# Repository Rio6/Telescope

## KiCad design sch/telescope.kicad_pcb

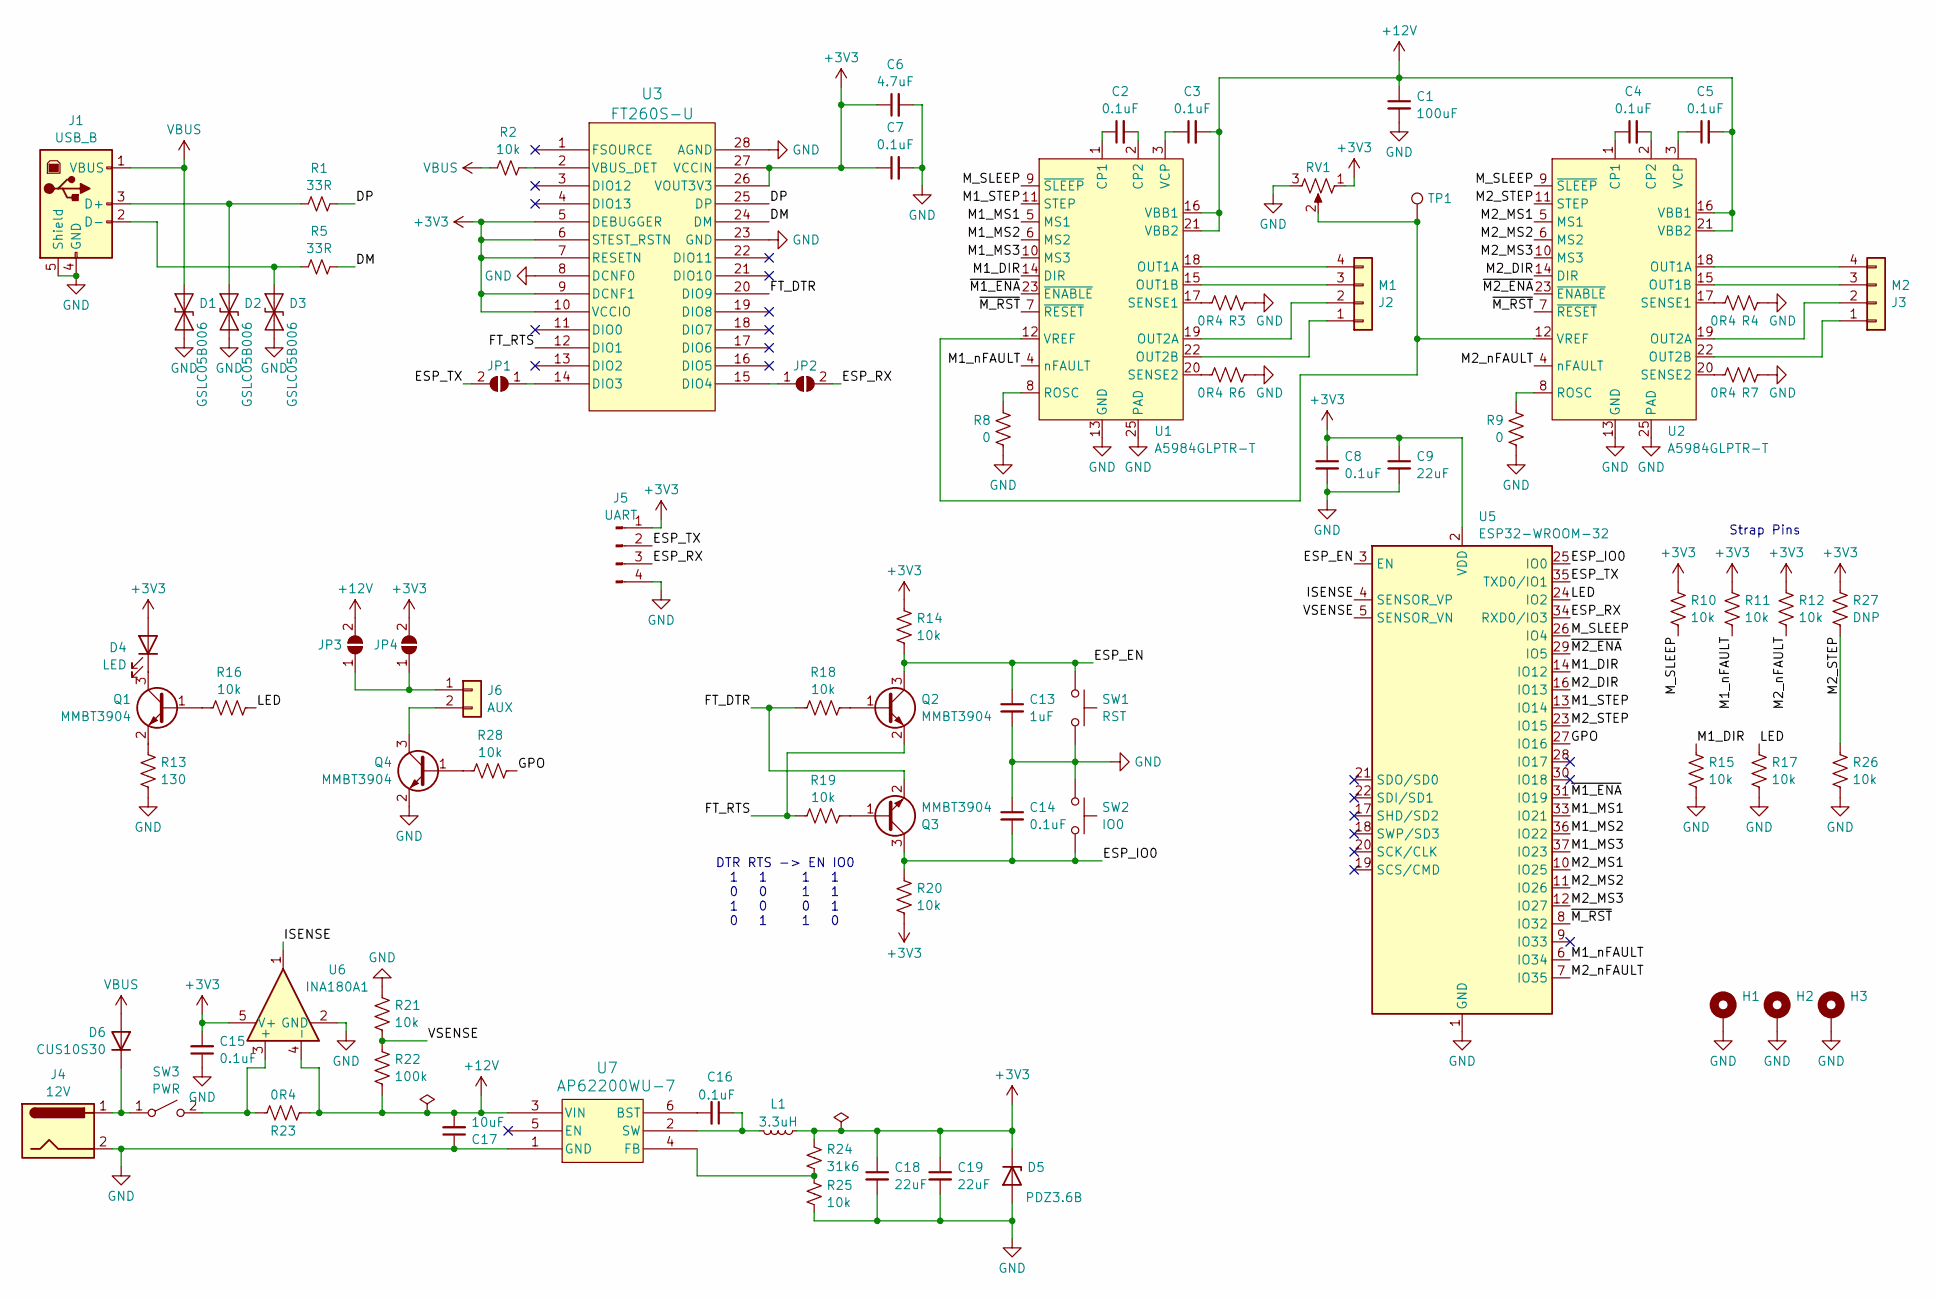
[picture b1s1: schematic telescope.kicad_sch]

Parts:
C1: 100uF; C_Radial_D5.0mm_H7.0mm_P2.00mm
C2, C3, C4, C5, C7, C8, C14, C15, C16: 0.1uF; C_0805_2012Metric_Pad1.18x1.45mm_HandSolder; Digikey PN 311-1140-1-ND
C6: 4.7uF; C_0805_2012Metric_Pad1.18x1.45mm_HandSolder; Digikey PN 1276-1244-1-ND
C9, C18, C19: 22uF; C_0805_2012Metric_Pad1.18x1.45mm_HandSolder; Digikey PN 1276-6687-1-ND
C13: 1uF; C_0805_2012Metric_Pad1.18x1.45mm_HandSolder; Digikey PN 311-1140-1-ND
C17: 10uF; C_0805_2012Metric_Pad1.18x1.45mm_HandSolder
D1, D2, D3: GSLC05B006; D_SOD-323_HandSoldering; Digikey PN 4786-GSLC05B006CT-ND
D4: LED; LED_1206_3216Metric_Pad1.42x1.75mm_HandSolder; Digikey PN 3147-T1341USD-30C000112U1930CT-ND
D5: PDZ3.6B; D_SOD-323_HandSoldering
D6: CUS10S30; D_SOD-323_HandSoldering
H1, H2, H3: MountingHole_Pad; MountingHole_3.2mm_M3_Pad
J1: USB_B; USB_B_OST_USB-B1HSxx_Horizontal; Digikey PN ED2982-ND
J2: M1; JST_PH_S4B-PH-K_1x04_P2.00mm_Horizontal; Digikey PN 455-1721-ND
J3: M2; JST_PH_S4B-PH-K_1x04_P2.00mm_Horizontal; Digikey PN 455-1721-ND
J4: 12V; CUI_PJ-037B; Digikey PN CP-037B-ND
J5: UART; PinHeader_1x04_P2.54mm_Vertical
J6: AUX; JST_PH_B2B-PH-K_1x02_P2.00mm_Vertical
JP1, JP2, JP3, JP4: SolderJumper_2_Open; SolderJumper-2_P1.3mm_Open_TrianglePad1.0x1.5mm
L1: 3.3uH; L_0805_2012Metric_Pad1.15x1.40mm_HandSolder
Q1, Q2, Q3, Q4: MMBT3904; SOT-23
R1, R5: 33R; R_0805_2012Metric_Pad1.20x1.40mm_HandSolder; Digikey PN RMCF0805JT33R0CT-ND
R2, R10, R11, R12, R14, R15, R16, R17, R18, R19, R20, R21, R26, R28: 10k; R_0805_2012Metric_Pad1.20x1.40mm_HandSolder
R3, R4, R6, R7, R23: 0R4; R_1206_3216Metric_Pad1.30x1.75mm_HandSolder; Digikey PN 283-MFHA1206R4000FCCT-ND
R8, R9: 0; R_0805_2012Metric_Pad1.20x1.40mm_HandSolder; Digikey PN 311-0.0ARCT-ND
R13: 130; R_0805_2012Metric_Pad1.20x1.40mm_HandSolder
R22: 100k; R_0805_2012Metric_Pad1.20x1.40mm_HandSolder
R24: 31k6; R_0805_2012Metric_Pad1.20x1.40mm_HandSolder; Digikey PN 311-31.6KCRCT-ND
R25: 10k; R_0805_2012Metric_Pad1.20x1.40mm_HandSolder; Digikey PN RMCF0805FT33K2CT-ND
R27: DNP; R_0805_2012Metric_Pad1.20x1.40mm_HandSolder
RV1: R_Potentiometer_US; Potentiometer_Bourns_TC33X_Vertical
SW1: RST; SW_TS04-66-43-BK-160-SMT; Digikey PN 2223-TS04-66-43-BK-160-SMT-ND
SW2: IO0; SW_TS04-66-43-BK-160-SMT; Digikey PN 2223-TS04-66-43-BK-160-SMT-ND
SW3: PWR; R13-66
TP1: TestPoint; TestPoint_Pad_D1.5mm
U1, U2: A5984GLPTR-T; TSSOP-24-1EP_4.4x7.8mm_P0.65mm_EP3.2x5mm; Digikey PN 620-1787-1-ND
U3: FT260S-U; TSSOP28_FT260S_FTD-M; Digikey PN 768-1282-5-ND
U5: ESP32-WROOM-32
U6: INA180A1; SOT-23-5; Digikey PN 296-47652-1-ND
U7: AP62200WU-7; TSOT-23-6_HandSoldering

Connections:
+3V3: C6.1, C7.1, C8.1, C9.1, C15.2, C18.1, C19.1, D4.2 (A), D5.1 (K), J5.1, JP4.2 (B), L1.2, R10.1, R11.1, R12.1, R14.1, R20.2, R24.1, R27.2, RV1.1, U3.5 (DEBUGGER), U3.6 (STEST_RSTN), U3.7 (RESETN), U3.9 (DCNF1), U3.10 (VCCIO), U3.26 (VOUT3V3), U3.27 (VCCIN), U5.2 (VDD), U6.5 (V+)
+12V: C1.1, C3.2, C5.2, C17.2, JP3.2 (B), R22.2, R23.2, U1.16 (VBB1), U1.21 (VBB2), U2.16 (VBB1), U2.21 (VBB2), U6.4 (-), U7.3 (VIN)
/DM: R5.2, U3.24 (DM)
/DP: R1.2, U3.25 (DP)
/ESP_EN: C13.1, Q2.3 (C), R14.2, SW1.1, U5.3 (EN)
/ESP_IO0: C14.2, Q3.3 (C), R20.1, SW2.2, U5.25 (IO0)
/ESP_RX: J5.3, JP2.2 (B), U5.34 (RXD0/IO3)
/ESP_TX: J5.2, JP1.2 (B), U5.35 (TXD0/IO1)
/FT_DTR: Q3.2 (E), R18.1, U3.20 (DIO9)
/FT_RTS: Q2.2 (E), R19.1, U3.12 (DIO1)
/GPO: R28.2, U5.27 (IO16)
/ISENSE: U5.4 (SENSOR_VP), U6.1
/LED: R16.2, R17.1, U5.24 (IO2)
/M1_DIR: R15.1, U1.14 (DIR), U5.14 (IO12)
/M1_MS1: U1.5 (MS1), U5.33 (IO21)
/M1_MS2: U1.6 (MS2), U5.36 (IO22)
/M1_MS3: U1.10 (MS3), U5.37 (IO23)
/M1_STEP: U1.11 (STEP), U5.13 (IO14)
/M1_nFAULT: R11.2, U1.4 (nFAULT), U5.6 (IO34)
/M2_DIR: U2.14 (DIR), U5.16 (IO13)
/M2_MS1: U2.5 (MS1), U5.10 (IO25)
/M2_MS2: U2.6 (MS2), U5.11 (IO26)
/M2_MS3: U2.10 (MS3), U5.12 (IO27)
/M2_STEP: R26.2, R27.1, U2.11 (STEP), U5.23 (IO15)
/M2_nFAULT: R12.2, U2.4 (nFAULT), U5.7 (IO35)
/M_SLEEP: R10.2, U1.9 (~SLEEP), U2.9 (~SLEEP), U5.26 (IO4)
/VSENSE: R21.2, R22.1, U5.5 (SENSOR_VN)
/~M1_ENA: U1.23 (~ENABLE), U5.31 (IO19)
/~M2_ENA: U2.23 (~ENABLE), U5.29 (IO5)
/~M_RST: U1.7 (~RESET), U2.7 (~RESET), U5.8 (IO32)
GND: C1.2, C6.2, C7.2, C8.2, C9.2, C13.2, C14.1, C15.1, C17.1, C18.2, C19.2, D1.1 (A1), D2.1 (A1), D3.1 (A1), D5.2 (A), H1.1, H2.1, H3.1, J1.4 (GND), J1.5 (Shield), J4.2, J5.4, Q4.2 (E), R3.1, R4.1, R6.1, R7.1, R8.2, R9.2, R13.2, R15.2, R17.2, R21.1, R25.2, R26.1, RV1.3, SW1.2, SW2.1, U1.13 (GND), U1.24 (GND), U1.25 (PAD), U2.13 (GND), U2.24 (GND), U2.25 (PAD), U3.8 (DCNF0), U3.23 (GND), U3.28 (AGND), U5.1 (GND), U5.15 (GND), U5.38 (GND), U5.39 (GND), U6.2 (GND), U7.1 (GND)
unnamed: D2.2 (A2), J1.3 (D+), R1.1
unnamed: D3.2 (A2), J1.2 (D-), R5.1
unnamed: D4.1 (K), Q1.3 (C)
unnamed: D6.1 (K), J4.1, SW3.1 (A)
unnamed: J2.1, U1.22 (OUT2B)
unnamed: J2.2, U1.19 (OUT2A)
unnamed: J2.3, U1.15 (OUT1B)
unnamed: J2.4, U1.18 (OUT1A)
unnamed: J3.1, U2.22 (OUT2B)
unnamed: J3.2, U2.19 (OUT2A)
unnamed: J3.3, U2.15 (OUT1B)
unnamed: J3.4, U2.18 (OUT1A)
unnamed: J6.1, JP3.1 (A), JP4.1 (A)
unnamed: J6.2, Q4.3 (C)
unnamed: JP1.1 (A), U3.14 (DIO3)
unnamed: JP2.1 (A), U3.15 (DIO4)
unnamed: Q1.1 (B), R16.1
unnamed: Q1.2 (E), R13.1
unnamed: Q2.1 (B), R18.2
unnamed: Q3.1 (B), R19.2
unnamed: Q4.1 (B), R28.1
unnamed: R23.1, SW3.2 (B), U6.3 (+)
unnamed: C2.1, U1.1 (CP1)
unnamed: C2.2, U1.2 (CP2)
unnamed: R8.1, U1.8 (ROSC)
unnamed: R3.2, U1.17 (SENSE1)
unnamed: R6.2, U1.20 (SENSE2)
unnamed: C3.1, U1.3 (VCP)
unnamed: RV1.2, TP1.1, U1.12 (VREF), U2.12 (VREF)
unnamed: C4.1, U2.1 (CP1)
unnamed: C4.2, U2.2 (CP2)
unnamed: R9.1, U2.8 (ROSC)
unnamed: R4.2, U2.17 (SENSE1)
unnamed: R7.2, U2.20 (SENSE2)
unnamed: C5.1, U2.3 (VCP)
unnamed: R2.2, U3.2 (VBUS_DET)
unnamed: C16.2, U7.6 (BST)
unnamed: R24.2, R25.1, U7.4 (FB)
unnamed: C16.1, L1.1, U7.2 (SW)
VBUS: D1.2 (A2), D6.2 (A), J1.1 (VBUS), R2.1

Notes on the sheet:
Strap Pins
DTR RTS -> EN IO0 1 1 1 1 0 0 1 1 1 0 0 1 0 1 1 0

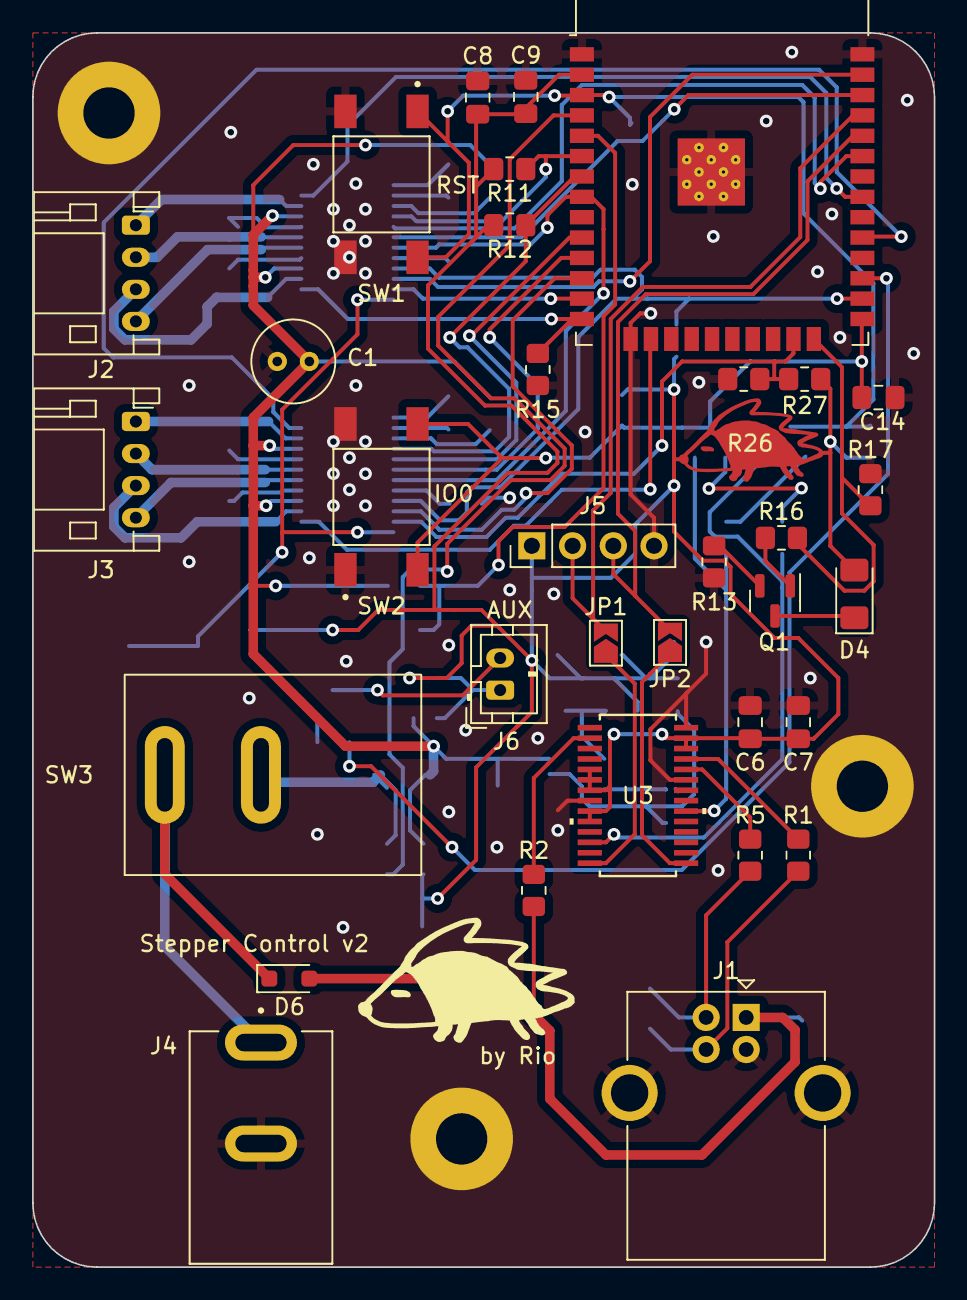
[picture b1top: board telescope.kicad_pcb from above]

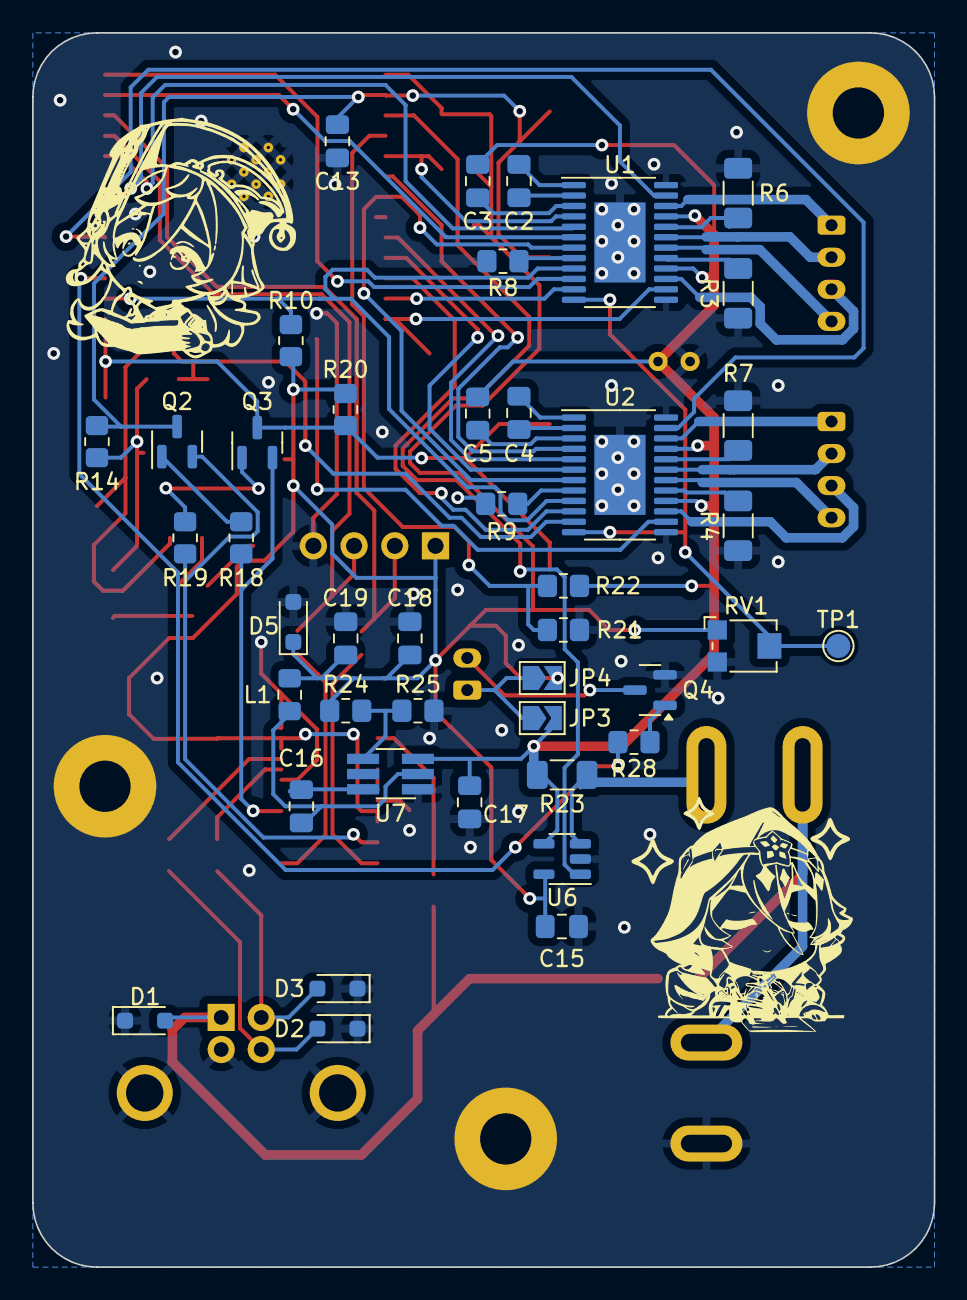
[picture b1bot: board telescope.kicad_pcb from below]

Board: 2 copper layers, 56.2 x 77.0 mm, 79 parts (43 on the bottom side), 71 nets.

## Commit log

2024-04-28 initial schematics
2024-04-28 pin assignment
2024-05-20 add isense and vsense, start layout
2024-05-26 layout, route, and add digikey numbers
2024-05-26 fix digikey part numbers
2024-05-26 add some more silkscreen
2024-05-26 generate gerbers
2024-06-15 fix feedback resistor value
2024-10-14 fix missing copper layer logo
2024-10-14 firmware blinky
2024-10-14 add series resistor to led bjt
2024-12-16 add support for automatic reset via gpiod
2024-12-20 update project configs
2024-12-20 stepper module
2024-12-25 wip synscan protocol parser
2024-12-26 increase reset capacitor value
2024-12-26 add tool for debugging serial protocol
2024-12-26 synscan protocol parser
2024-12-27 stepper driver using rmt wip
2024-12-27 add cad files
2024-12-27 update sdkconfig
2024-12-27 stepper driver wip
2024-12-29 fix channel->stepper conv and add more command support
2024-12-30 switch from rmt to mcpwm since esp32 does not support rmt loop count
2025-01-03 fix busy flag and payload parsing
2025-01-03 put mcpwm interrupt in iram
2025-01-06 wip wifi
2025-01-12 try a different approach for wifi configuration
2025-01-13 make synscan parser be called by other tasks
2025-04-26 Switch to driver that supports native esptools
2025-04-26 Fix wifi command parsing
2025-04-26 Enable debug build and update monitor EOL
2025-04-27 Use built-in function to retry wifi connection and add IP query
2025-04-30 pull down bootstrap pin for serial logging
2025-04-30 disable bootloader logging
2025-04-30 add eol filter
2025-07-15 add udp server interface
2025-07-16 use synscan udp port
2025-08-10 split motor driver enable lines and increase motor trace width
2025-08-11 add overvolt protection, USB power, and GPO to schematics
2025-08-11 add vsense and isense support
2025-08-11 wip separate ena lines in firmware
2025-08-12 update pcb
2025-08-13 switch to jst and generate v2 gerbers
2025-12-25 don't panic on error
2025-12-25 add heartbeat led
2025-12-27 add reset control pull down
2025-12-27 switch to non-aggregrated mcpwm generator function
2025-12-27 add cmake files to gitignore
2025-12-28 fix synscan data format and add stepper fast mode
2025-12-28 Add 0x800000 offset to position and goto
2025-12-31 wip: esp_ap compatible commands
2025-12-31 increase serial-to-udp.py read size
2025-12-31 implement esp_at compatible wifi commands
2026-01-03 reduce server error severity
2026-01-03 add an idle state to synscan parser and rework state machine
2026-01-03 Measure and update gear ratio
    they're off by 1 between each axis..
2026-01-12 implement synscan stub for eqmod
2026-01-12 add tripod head cad
2026-04-11 update esp-idf version
2026-04-15 implement stepper acceleration
